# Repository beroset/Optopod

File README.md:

# Purpose
The purpose for the Optopod is to allow a Raspberry Pi or other small microcontroller to communicate with a meter using either the ANSI C12.18 or IEC 62056-21 communications standard.  Both standards use a very simple infrared (IR) optical communications protocol and the physical attributes of the port are nearly identical.  In particular, there are only two significant differences:  the IEC protocol has the transmit on the right and receive on the left with a round port, while the ANSI protocol has the transmit on the left and receive on the right with a flat at the bottom of the otherwise round port.  The IEC version is shown in Figure 1.

In addition to simply operating as a probe, the circuit will also have an intercept feature.  That is, it is intended to be able to put the circuit between an optical probe attached to a computer and a meter.  This will allow the Raspberry Pi to "listen in" to the communications between programming and/or reading software and the meter, allowing the circuit to be used to capture that communications for later analysis and/or alter it on the fly.

# Design overview
The board is intended to be driven from a 3.3V power supply and communications.  The serial RX and TX lines of a Raspberry Pi will be used to receive/transmit via the optical port circuits on opposite sides of the board.  A six-pin connector will be used for +3.3V, GND, RX1, TX1, RX2 and TX2 lines.   To make the assembly as simple as possible, only the IR LED and IR phototransistor will be on the opposite side of the board.  All other parts will be on the front of the board, allowing reflow soldering of all but those two parts.

## Transmit circuit

## Receive circuit

### Board design
As mentioned earlier, the board actually has two separate transmit circuits and two separate receive circuits so that the board may be used *between* an optical probe and meter to allow it to "listen in" on the conversation between, say, proprietary programming software and a meter.  For simplicity in manufacturing all of the surface mount parts are mounted on the front except for one of the IR diode/phototransistor pairs, designated D1 and Q1 on the schematic.  The bill of materials shown in the table below.  The total cost is $2.62.

 Item| Qty | Reference(s)  |    Value                                 | Price  |Ext Total
-----|-----|---------------|------------------------------------------|--------|----------
 1   | 2   |D1, D2         |IR LED Kingbright APTD3216F3C-P22         |$0.147  |$0.29
 2   | 1   |J1             |right angle 6pos hdr, 2.54mm              |$0.105  |$0.11
 3   | 2   |Q1, Q5         |IR phototrans Kingbright APTD3216P3C-P22  |$0.140  |$0.28
 4   | 4   |Q2, Q3, Q4, Q6 |TRANS NPN 45V 0.5A SOT23, BC817-40        |$0.049  |$0.20
 5   | 2   |R1, R6         |0402 SMD resistor 2.2K                    |$0.019  |$0.04
 6   | 2   |R2, R7         |0402 SMD resistor 330                     |$0.019  |$0.04
 7   | 2   |R3, R8         |0402 SMD resistor 5.1K                    |$0.019  |$0.04
 8   | 2   |R4, R9         |0402 SMD resistor 91                      |$0.019  |$0.04
 9   | 2   |R5, R10        |0402 SMD resistor 1.5K                    |$0.019  |$0.04
 10  | 1   |board          |Custom PCB                                |$1.550  |$1.55

### Rendered board image

### Schematic

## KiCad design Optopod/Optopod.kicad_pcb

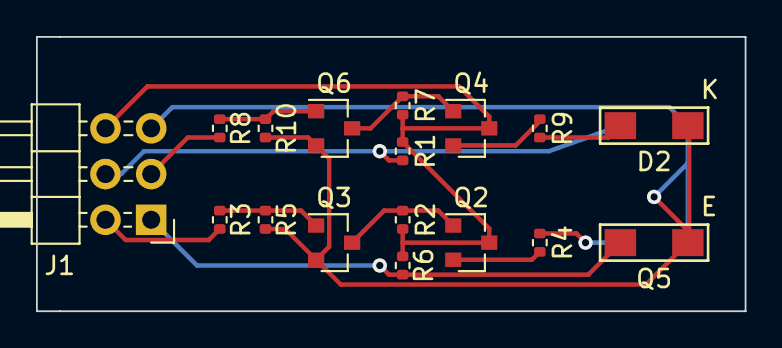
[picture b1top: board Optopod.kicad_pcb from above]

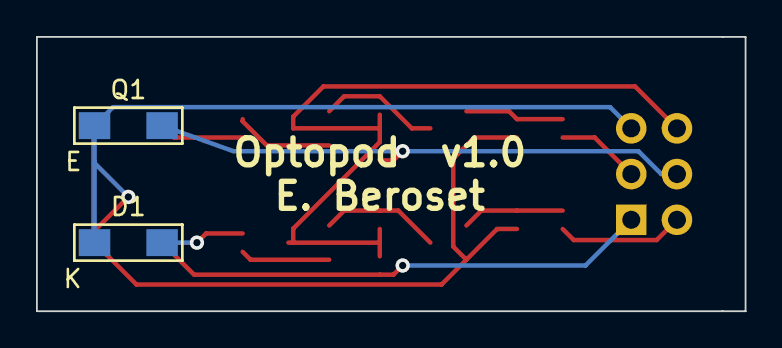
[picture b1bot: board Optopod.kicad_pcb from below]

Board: 2 copper layers, 39.4 x 15.2 mm, 19 parts (2 on the bottom side), 14 nets.

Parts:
D1, D2: APTD3216F3C-P22; LED_Kingbright_APTD3216
J1: Conn_02x03_Odd_Even; PinHeader_2x03_P2.54mm_Horizontal
Q1, Q5: APTD3216P3C-P22; LED_Kingbright_APTD3216
Q2, Q3, Q4, Q6: BC817; SOT-23
R1, R6: 2.2K; R_0402_1005Metric
R2, R7: 330; R_0402_1005Metric
R3, R8: 5.1k; R_0402_1005Metric
R4, R9: 91; R_0402_1005Metric
R5, R10: 1.5k; R_0402_1005Metric

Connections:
+3V3: J1.6, Q2.3, Q4.3, R1.1, R2.1, R6.1, R7.1
GND: D1.1, D2.1, J1.5, Q1.1, Q3.2, Q5.1, Q6.2, R5.2, R10.2
unnamed: D1.2, R4.2
unnamed: D2.2, R9.2
unnamed: Q2.1, Q3.3, R2.2
unnamed: Q2.2, R4.1
unnamed: Q3.1, R3.1, R5.1
unnamed: Q4.1, Q6.3, R7.2
unnamed: Q4.2, R9.1
unnamed: Q6.1, R8.1, R10.1
RX1: J1.4, Q1.2, R1.2
RX2: J1.1, Q5.2, R6.2
TX1: J1.2, R3.2
TX2: J1.3, R8.2

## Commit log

2021-03-23 Create initial design
2021-03-25 Add updated renders front and back
2021-03-25 Update schematic and layout
2021-03-25 Update documentation for board.
2021-03-25 Update name to Optopod
2021-03-25 Change name of directory to Optopod
2021-03-25 Move images files.
2021-03-25 Add bill of materials.
2021-03-25 Rename md file to README
2021-03-25 Attempt to clean up formatting for github
2021-03-25 Simplify readme and move design details to separate doc.
2021-03-25 update schematic
2021-03-25 Fix up readme file
2021-03-25 Rename files to current project name
2021-03-25 Rename more files.
2021-03-25 Update files for simulation.
2021-03-25 Update naming and documentation.
2021-03-25 Add details for design documentation.
2021-03-25 Adjust solder paste clearance to -0.06mm
2021-03-25 Create LICENSE
2021-03-26 Change solder mask setting to -0.06mm
